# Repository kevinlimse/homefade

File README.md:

# homefade

Wall-mounted motorized fader for Home Assistant (brightness / colour temp, live two-way sync), 18 mm pitch so 2–3 sit side by side.

- `HANDOVER.md` – status, chosen parts, open items, how to set up a new machine.
- `pcb/` – KiCad project, Gerbers/BOM/CPL (`pcb/fab/`), ESPHome firmware (`pcb/esphome/`), generator scripts (`pcb/gen/`).
- `cad/` – FreeCAD fader model and PCBA assembly (FCStd + STEP).
- `freecad-macros/` – macros to copy into `%APPDATA%\FreeCAD\v1-1\Macro\`.

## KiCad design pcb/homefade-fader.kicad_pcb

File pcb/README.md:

# homefade fader controller v1.1

One small board per Alps RS60N11M9A0F motor fader. It connects the fader to Home Assistant through ESPHome, with live sync both ways.

## Why one board per fader (and not one board for three)

* **Width = fader width.** The board is **18.0 mm wide**, the same as the fader frame, and hangs directly on the fader's own pins. Faders can sit side by side at an **18 mm pitch** (frames touching). A 3-fader board would fix the spacing forever and still be ≥ 54 mm wide.
* **Flat back.** Every SMD part sits on the side facing the fader, in the space under its body (the fader seats 26 mm below the panel, and most of that is empty). The back of the PCB is flat apart from the soldered fader pins, so total depth is about **26 mm + 1.6 mm PCB + ~1.5 mm of pin tails**.
* **One USB-C feeds several.** Plug USB-C into one board. Wire its **J2 (VBUS/GND)** pads to J2 on the next board(s). Only plug one USB-C into a chained set. A 9 V / 2 A (18 W+) charger is plenty for 3 faders.
* Each fader becomes its own ESPHome device. They're independent, and one bad board doesn't take the others down. An ESP32-S3 costs about $3.

Board: **18.0 × 120.0 mm**, **4 layers** (inner 1 = solid GND plane), 1.6 mm. Coordinates match the FreeCAD model (X = 0 at the fader's 3T end). The board runs 6 mm past the 3T end for the USB-C and 7.5 mm past the 1T end, so the Wi-Fi antenna isn't under the motor.

## Blocks

| Block | Part | Notes |
|---|---|---|
| Power in | USB-C (HRO TYPE-C-31-M-12) + **CH224A** PD sink | Asks for **9 V** (R3 = 6.8 k). For 12 V, fit 24 k (C25769) and set `max_duty: 0.83`. Never leave R3 open: open = 20 V, which kills the TB6612. Most chargers do 9 V; many (Apple, for example) don't offer 12 V. |
| ESD | USBLC6-2SC6 | On D+/D− |
| 3.3 V | TPS563201 buck, 3.3 µH, 33 k/10 k | 4.5–17 V in |
| Motor | **TB6612FNG**, both bridges in parallel | 15 V max; brake/coast; STBY pulled low while the ESP boots |
| MCU | **ESP32-S3-MINI-1-N8** | Native USB on the same USB-C for flashing and logs (no USB-UART chip). Built-in capacitive touch is used for the fader's touch track. |
| Fader | pot (via 1 k from 3V3 so the wiper tops out at ~3.0 V), RC filter → GPIO1; touch "T" → GPIO2 | Frame lugs to GND |
| Extra | BOOT/RESET buttons, LED (GPIO10), VBUS sense (GPIO9, ÷11), PD power-good (GPIO8) | The firmware won't drive the motor without PD power (for example when it's only on a PC port at 5 V) |
| Position LED bar | 10 × **SK6812SIDE-A** side-firing RGB LEDs (GPIO17, 100 Ω), 2nd TPS563201 at **4.5 V** (33k/6.8k, 4×4 mm 3.3 µH) | One LED per 10 % of travel along the +Y edge, light exits sideways from under the fader. At 4.5 V the LED input threshold (0.65 × VDD = 2.9 V) is below the ESP's 3.3 V, so no level shifter. Worst case all-white ≈ 360 mA from 4.5 V |

GPIO map: 1 wiper ADC, 2 touch, 4 PWM, 5 IN1, 6 IN2, 7 STBY, 8 PD_PG, 9 VBUS sense, 10 LED, 17 LED bar data, 19/20 USB.

## Files

* `homefade-fader.kicad_pro / .kicad_sch / .kicad_pcb`: KiCad 7+ project. Schematic uses net labels.
* `board-routed.png`: top and bottom copper.
* `fab/homefade-fader-gerbers-JLCPCB.zip`: Gerbers and Excellon drill files, ready to upload (**4 layers**, 1.6 mm, JLC default stackup).
* `homefade.pretty`, `homefade.kicad_sym`: project footprints and symbols (fader footprint from the Alps drawing, Espressif's official ESP32-S3-MINI-1 footprint).
* `fab/BOM-JLCPCB.csv`, `fab/CPL-JLCPCB.csv`, `fab/BOM.md`: JLCPCB assembly files. Every part was in stock at LCSC on 2026-11-26.
* `esphome/homefade-fader.yaml`: firmware (validated with `esphome config`, ESPHome 2026.11).
* `gen/`: Python scripts that generate everything from `gen/design.py`. `route_all.sh` re-runs placement → Freerouting → finishing router → stitching.

## Status / before ordering

1. **v1.1 adds the position LED bar and goes to 4 layers.** With the LED row along one edge, a 2-layer board could not keep its ground pours joined (the motor driver's ground ended up on an island), so inner layer 1 is now a solid GND plane and inner layer 2 carries signals. Freerouting did the signals; `gen/ledbar_route.py` pre-routes the LED row (4.5 V rail under the LEDs, data hops just inboard, a GND via per LED). KiCad DRC: **0 unconnected pads, no clearance, width or hole errors**; only cosmetic silk and library-path warnings remain.
2. **LED footprint is [EST].** The SK6812SIDE-A land pattern is only drawn (not dimensioned in text) in the datasheet. I used 4 pads, 0.7 × 1.1 mm at 1.15 mm pitch at the rear of the 4.0 × 1.6 mm body, light out of the long front face, pin 1 = DIN. **Check it, and that each LED faces the board edge, in JLC's footprint/CPL preview before ordering.** Same for **U1 (CH224A ESSOP-10)** and **L1 (FXL0630)**.
3. The fader's under-body heights are **[EST]** in the FreeCAD model. Parts under the motor (x 66–92 mm) are ≤ 2.1 mm tall; the model gives ~5 mm of space. The LEDs sit at y 7.4–9.0 mm, just outside the motor bracket (±7 mm [EST]) at x 61–65 mm. Check against a real fader.
4. Antenna: keep metal off the board end past the fader (x > 106.5 mm). A metal faceplate 26 mm above will reduce range somewhat.
5. In HA, allow the device to perform Home Assistant actions (ESPHome integration → Configure).

## Firmware tuning (first boot)

1. Watch **Fader raw** in the logs at both ends of travel. Put the values in `adc_bottom` / `adc_top`.
2. Set `esp32_touch: setup_mode: true`, then touch and release the knob. Choose `touch_threshold` between the two values (S3 values *rise* when touched).
3. If the fader runs away from the target, set `motor_invert: "true"`. Raise `min_duty` if it stalls near the target; lower `kp` if it overshoots.
4. LED bar: if it fills from the wrong end, set `led_bar_reverse: "true"`. In HA, **Position bar** switches the LEDs and sets overall brightness; **Bar filled colour** (default green) and **Bar empty colour** (default dim red) are colour pickers for the part below and above the knob.

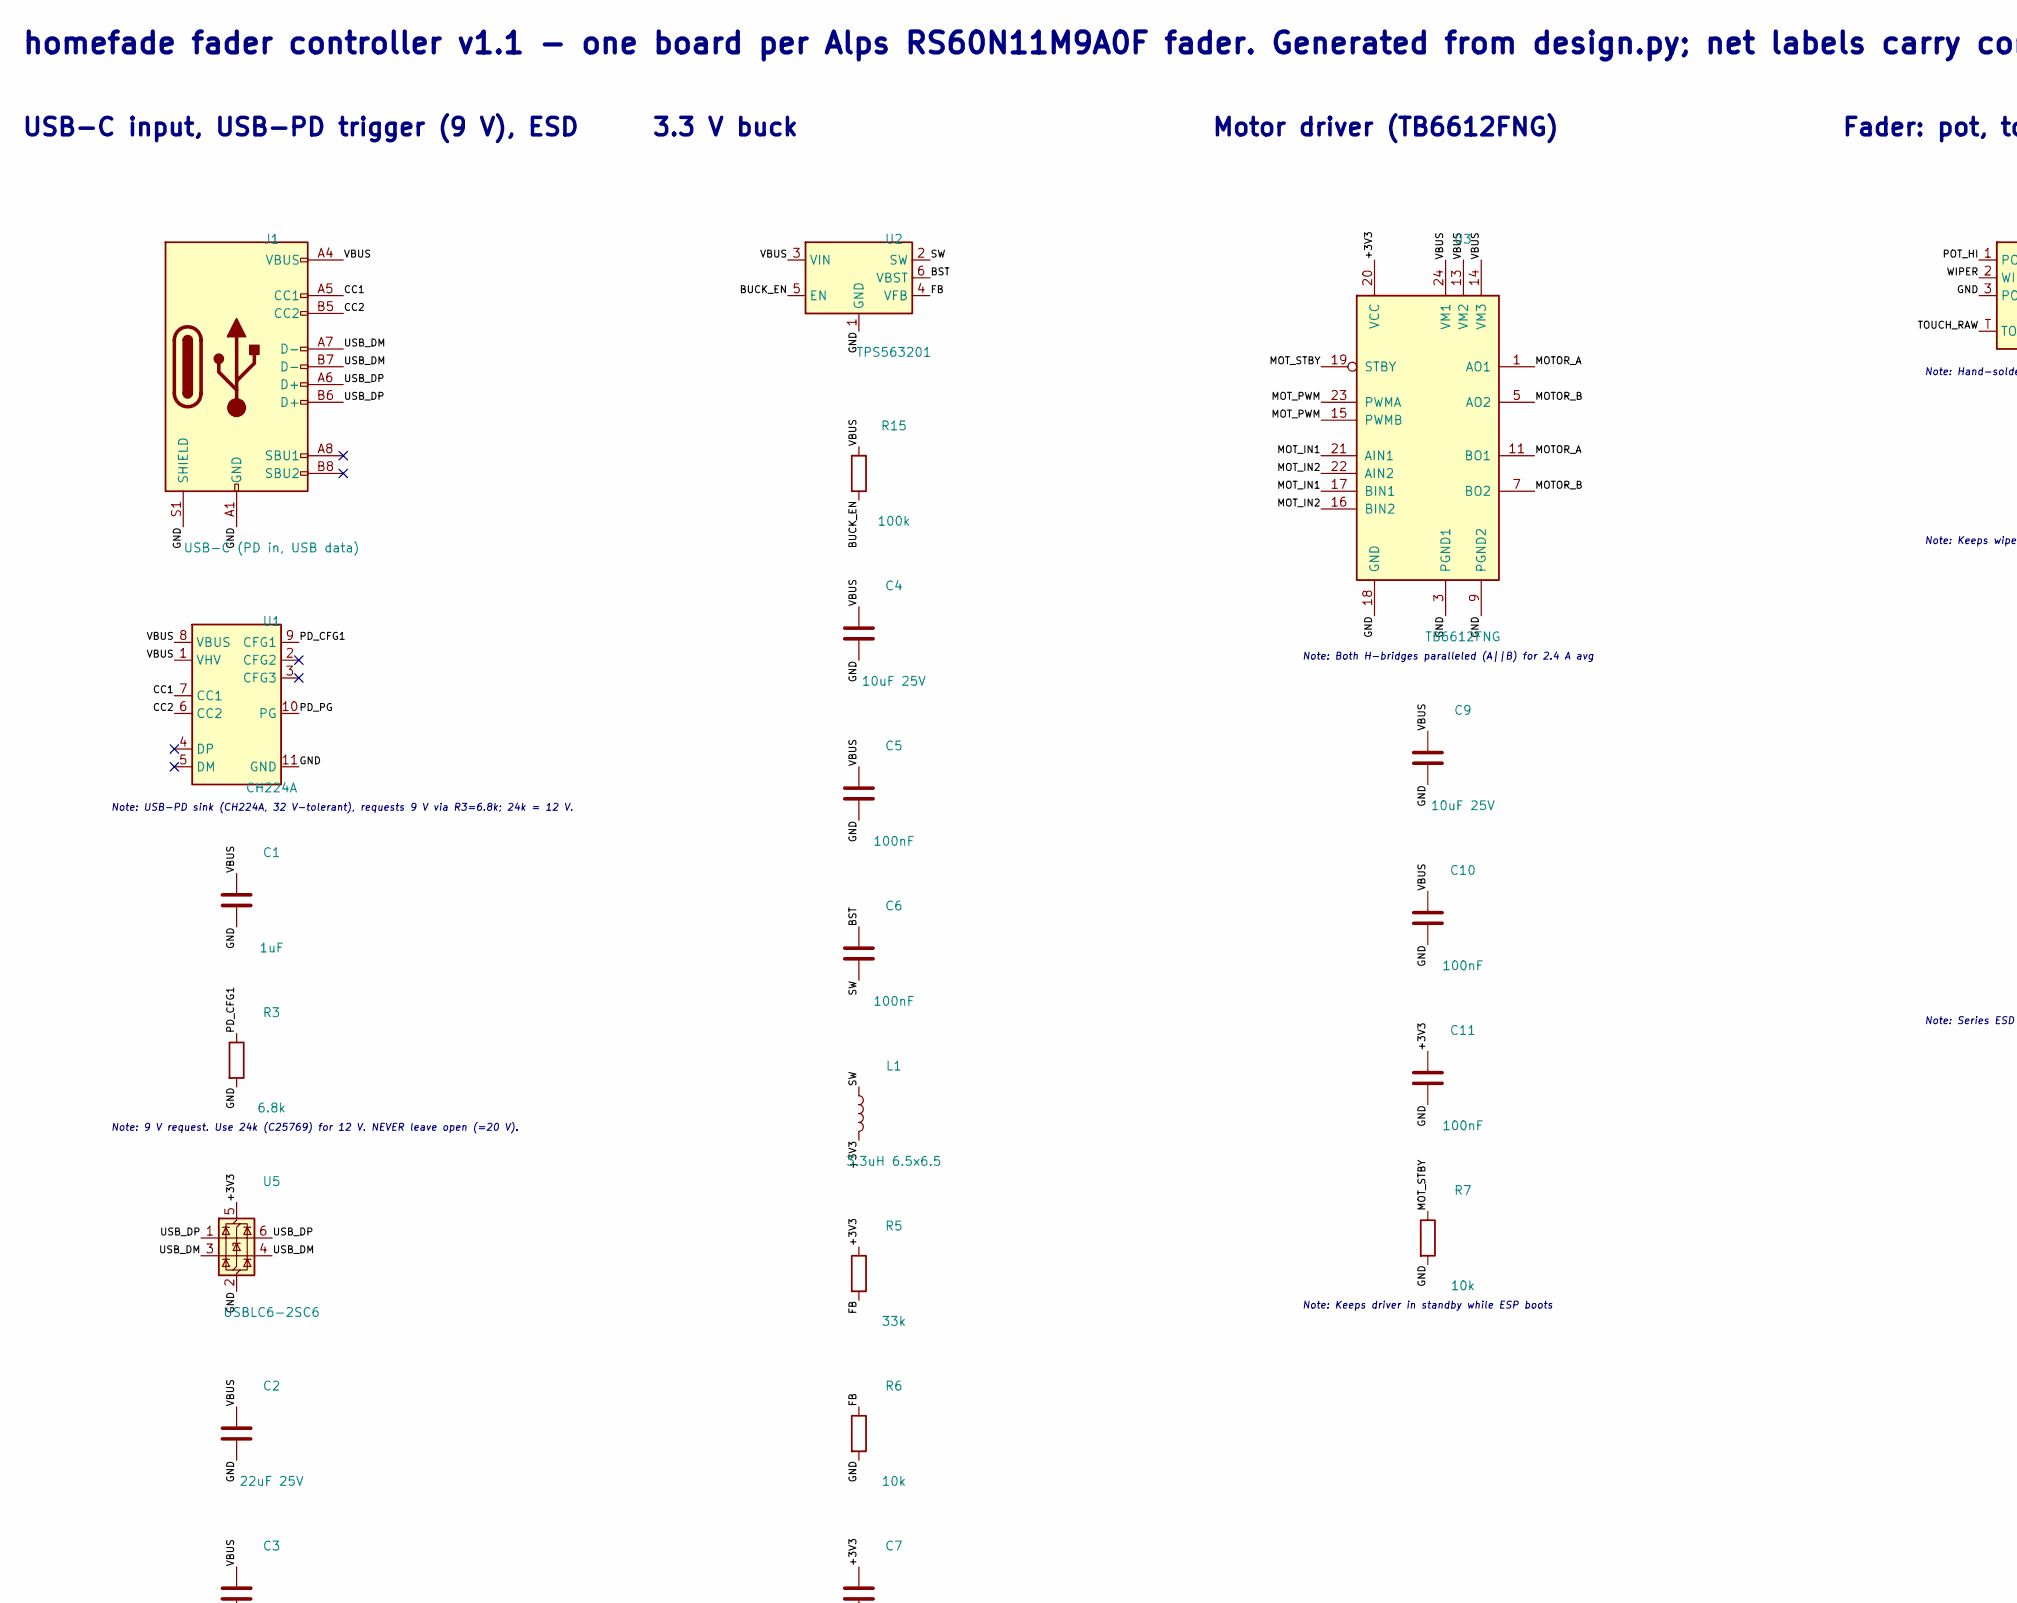
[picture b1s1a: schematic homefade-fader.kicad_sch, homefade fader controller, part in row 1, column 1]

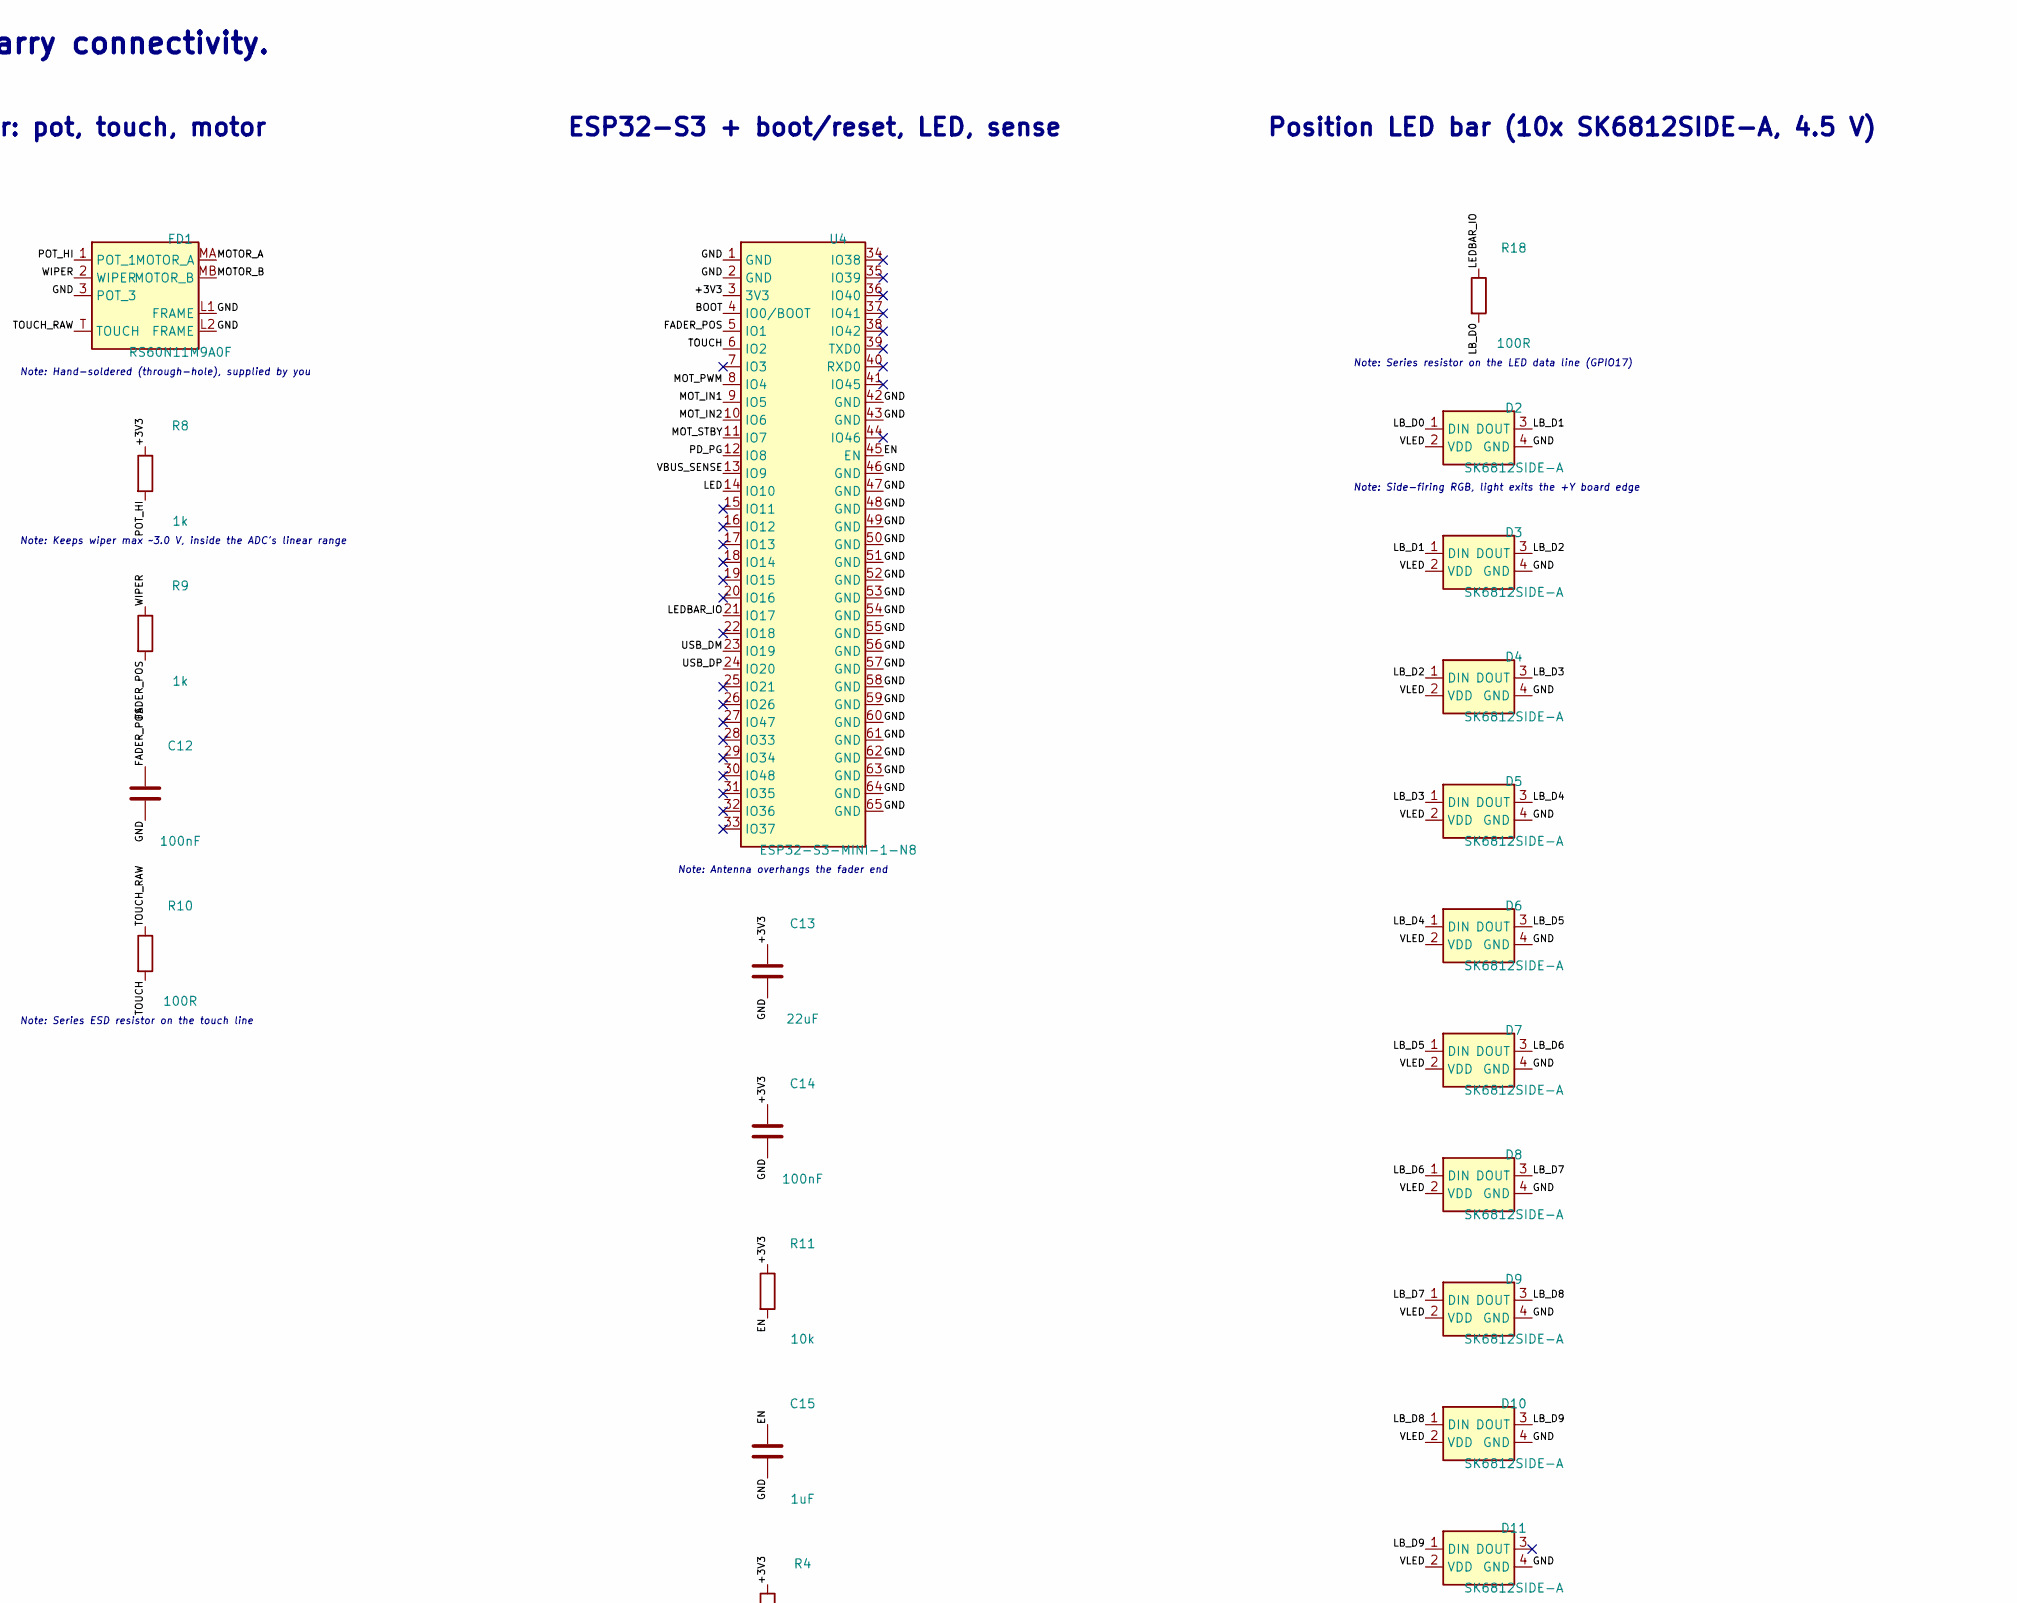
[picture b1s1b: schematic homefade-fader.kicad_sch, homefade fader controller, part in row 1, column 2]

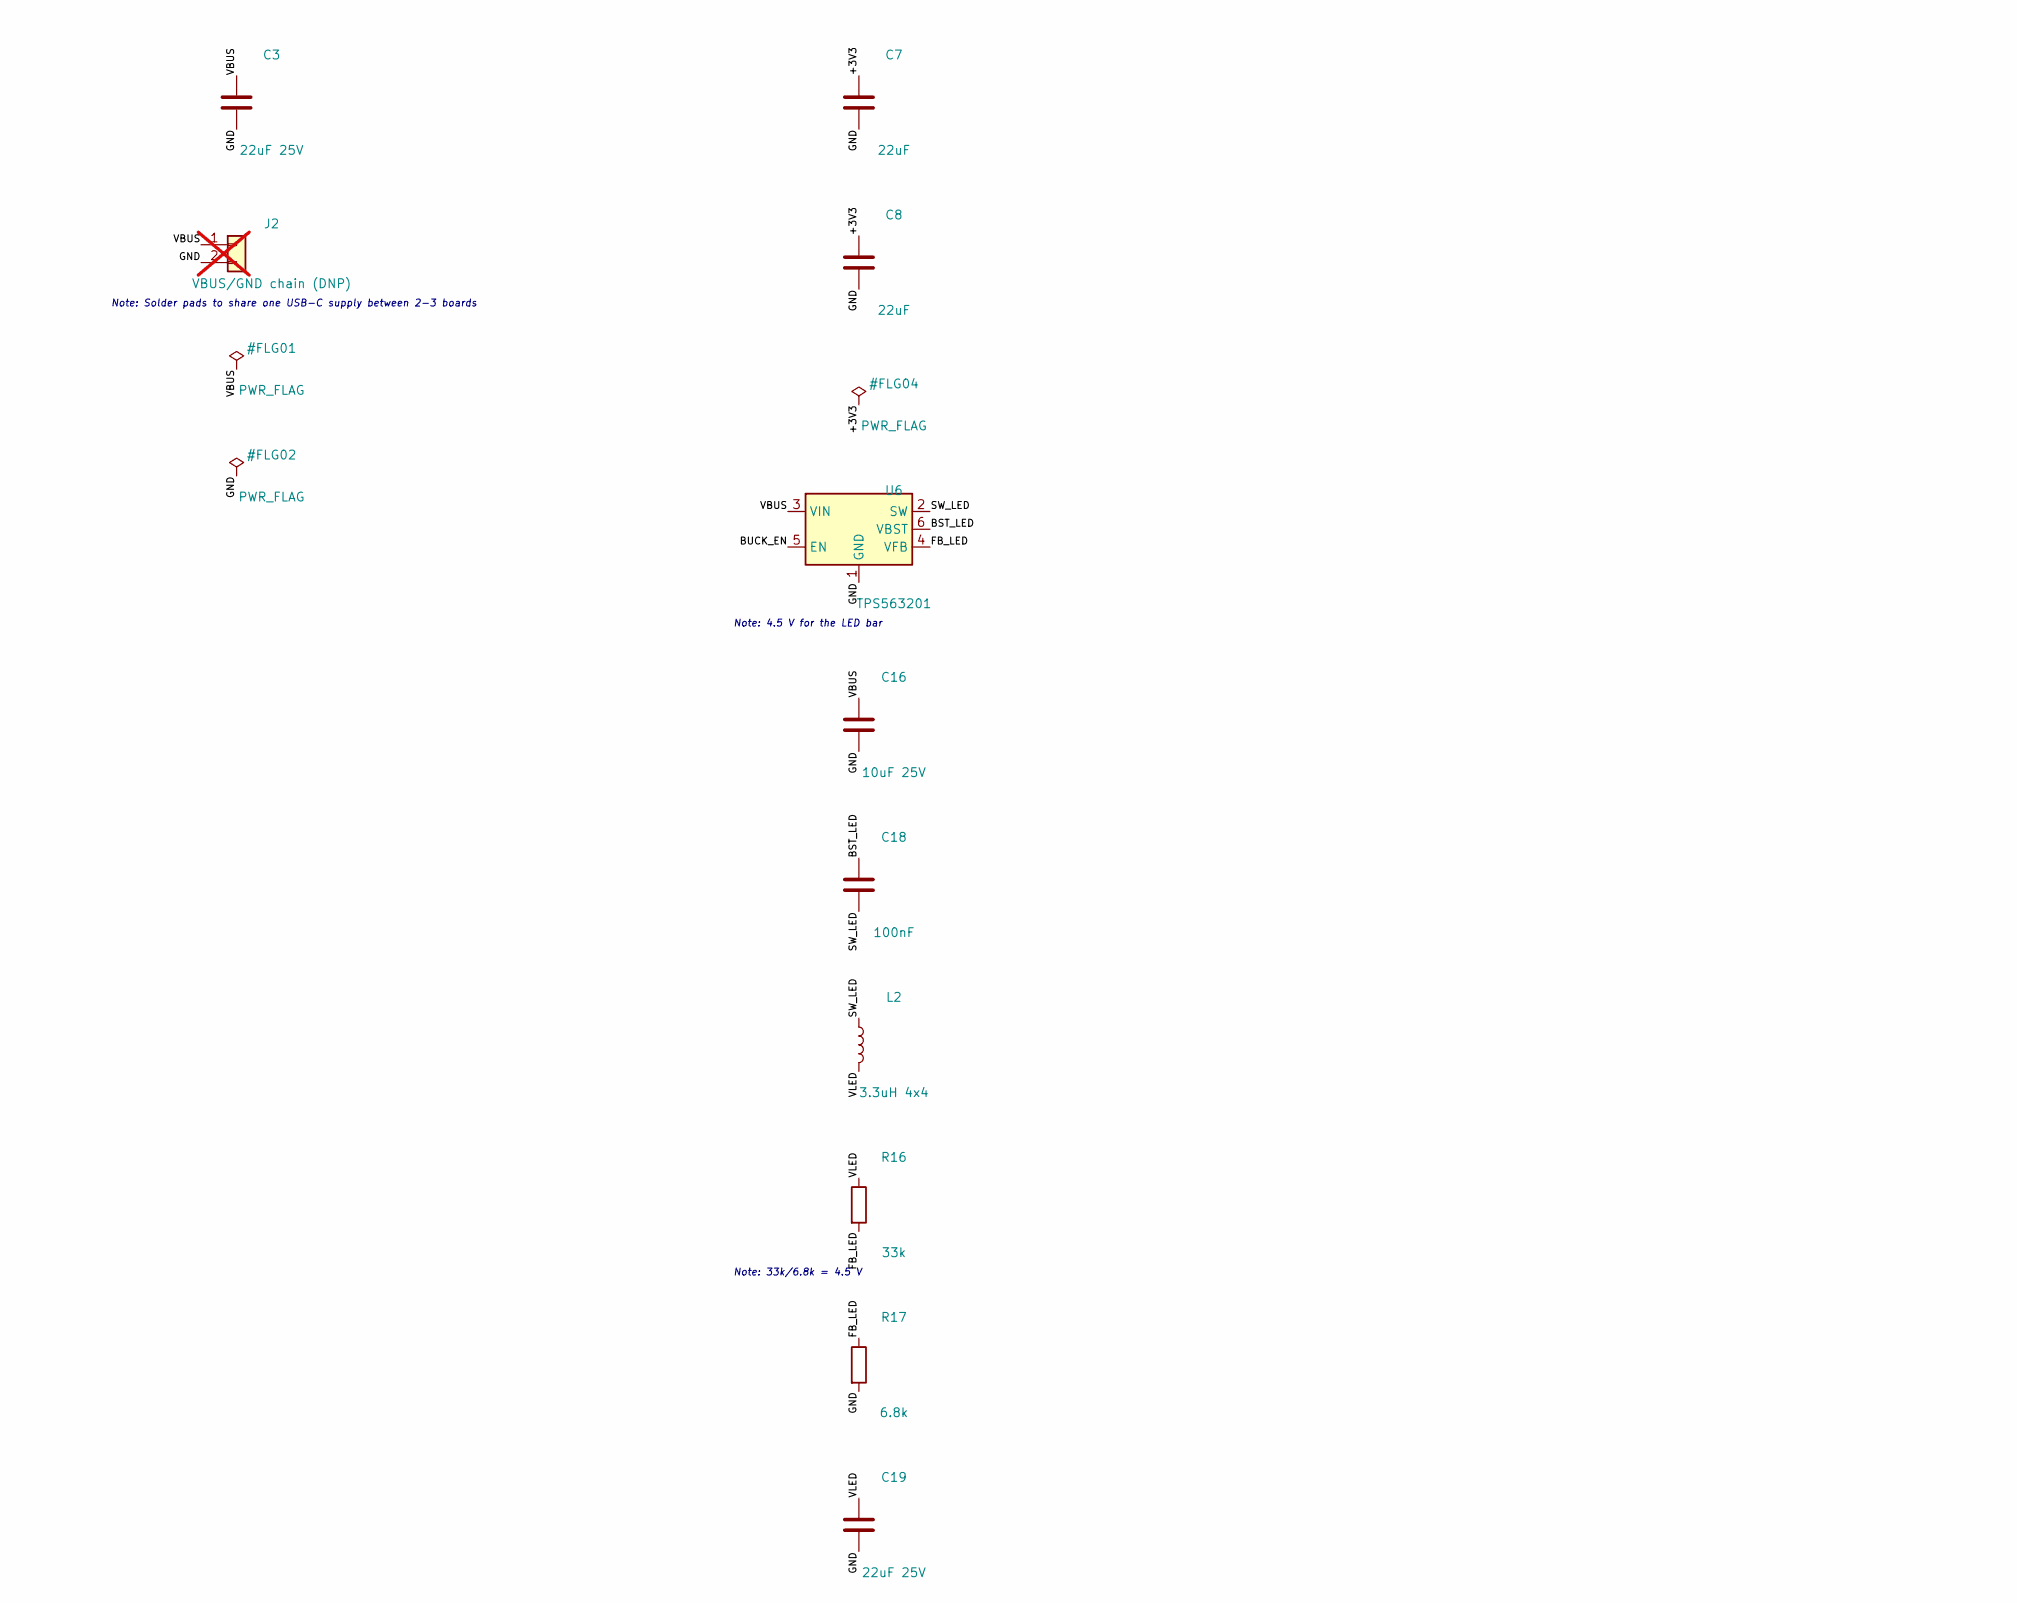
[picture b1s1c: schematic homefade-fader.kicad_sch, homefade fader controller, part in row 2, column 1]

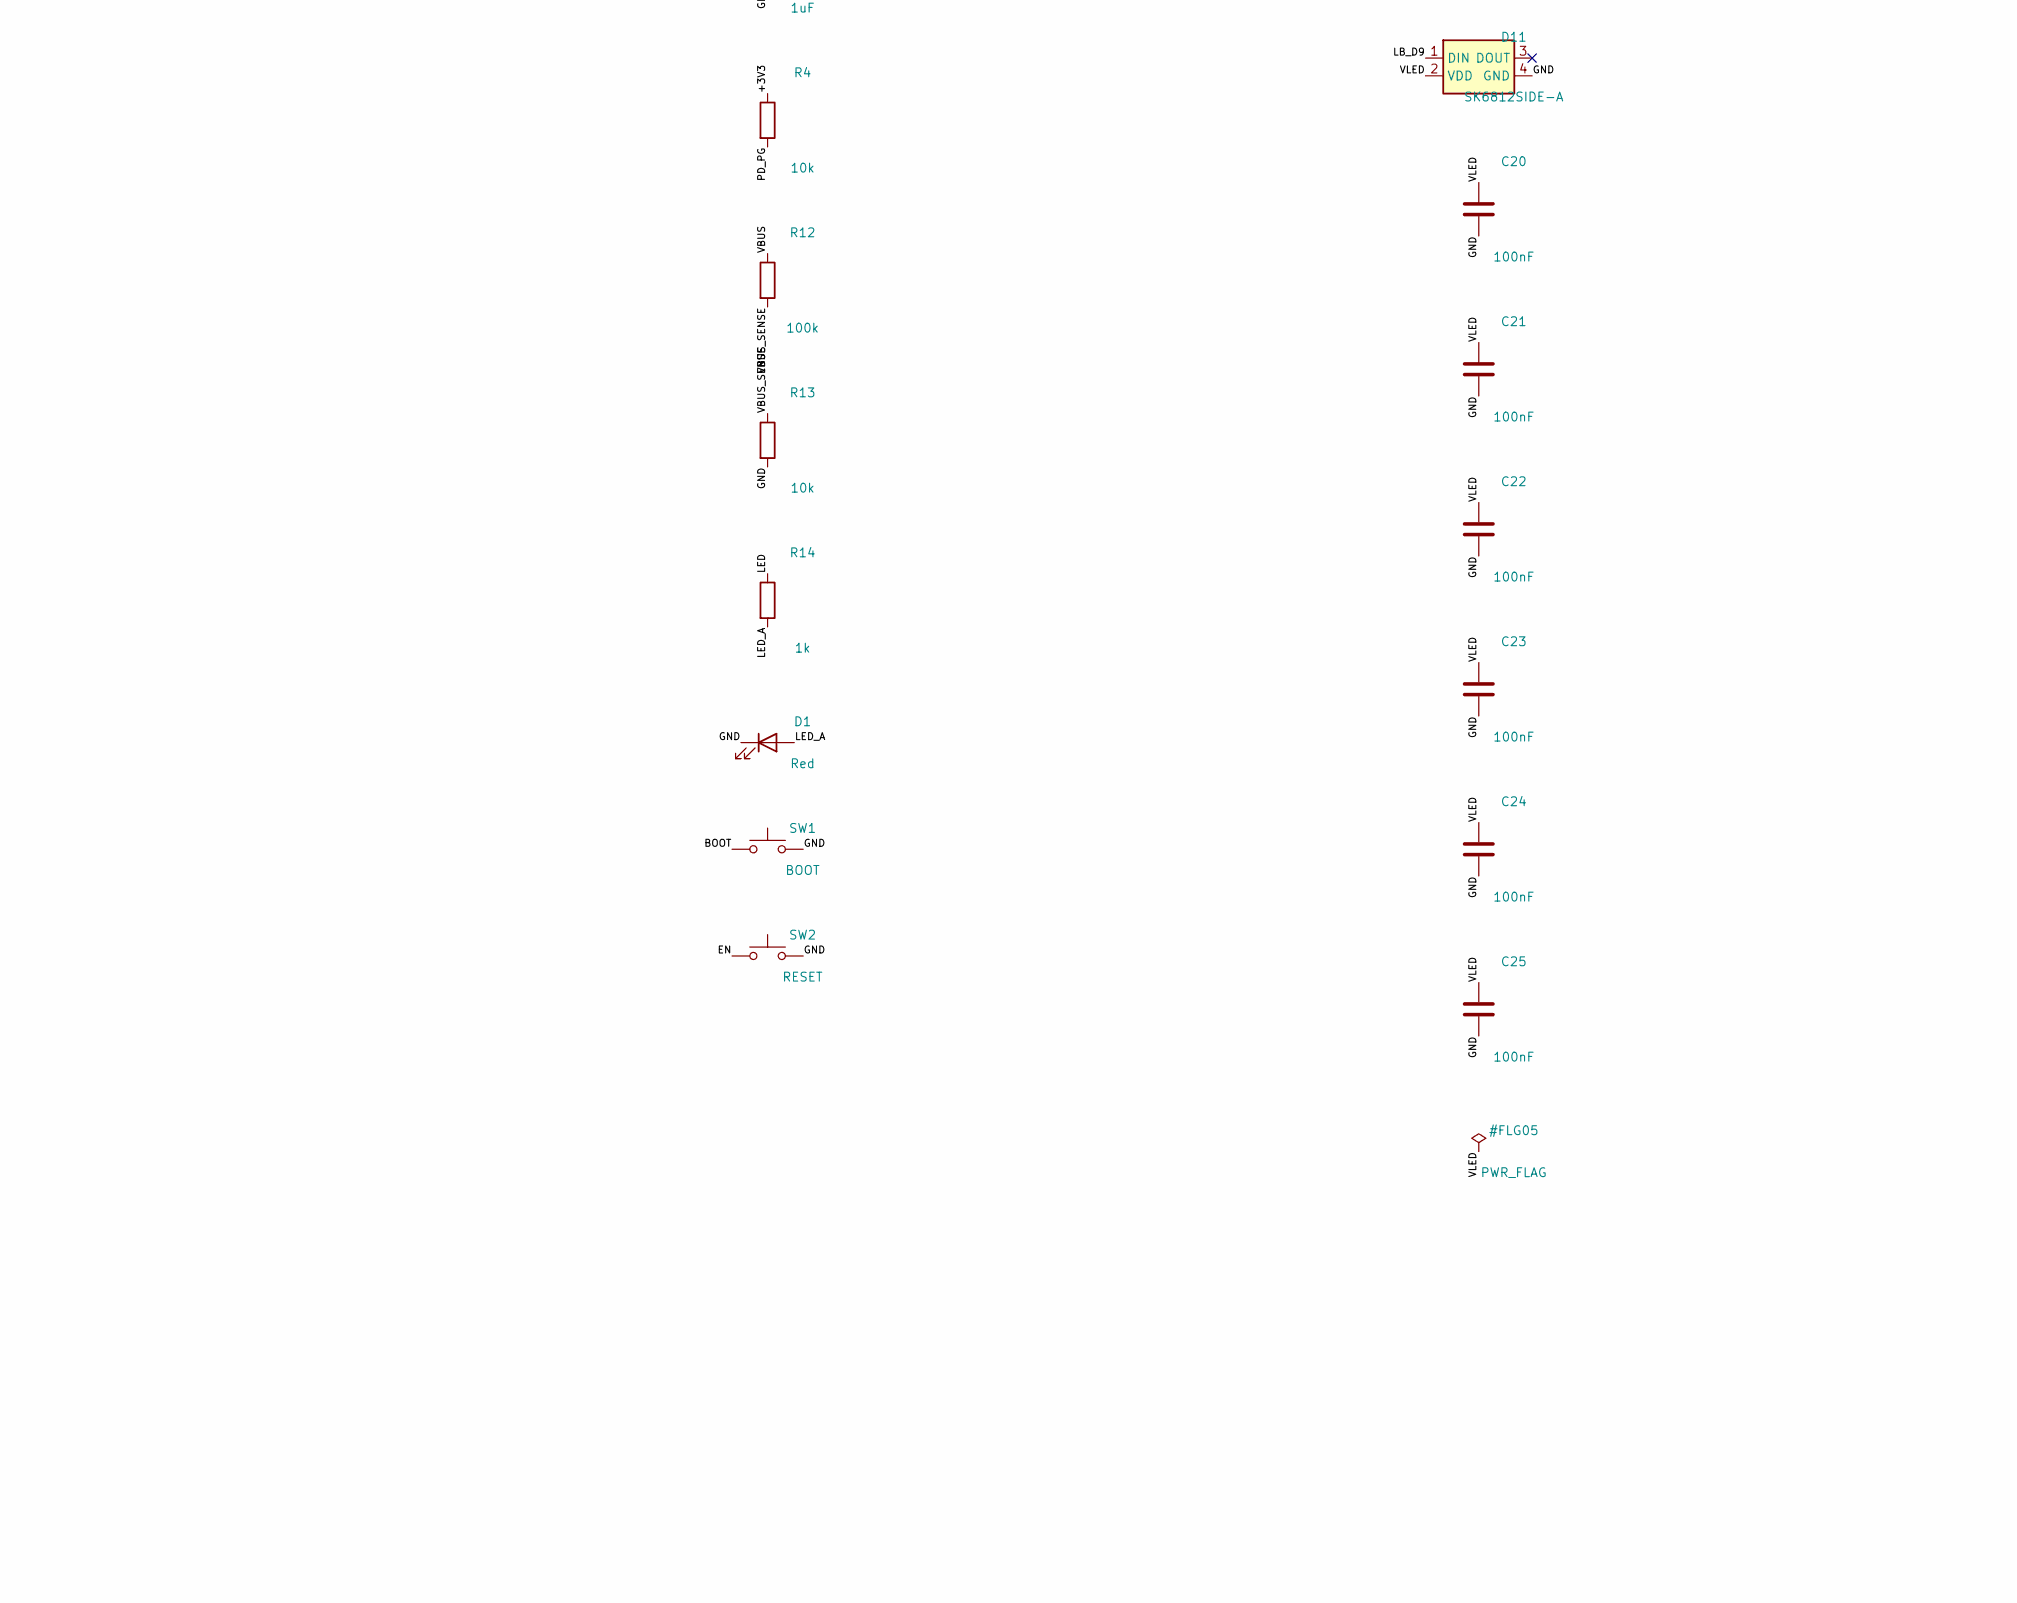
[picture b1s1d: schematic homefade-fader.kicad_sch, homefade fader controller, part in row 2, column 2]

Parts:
C1, C15: 1uF; C_0402_1005Metric; LCSC C83063
C2, C3, C19: 22uF 25V; C_0805_2012Metric; LCSC C45783
C4, C9, C16: 10uF 25V; C_0603_1608Metric; LCSC C96446
C5, C6, C10, C11, C12, C14, C18, C20, C21, C22, C23, C24, C25: 100nF; C_0402_1005Metric; LCSC C1525
C7, C8, C13: 22uF; C_0603_1608Metric; LCSC C59461
D1: Red; LED_0603_1608Metric; LCSC C2286
D2, D3, D4, D5, D6, D7, D8, D9, D10, D11: SK6812SIDE-A; LED_SK6812SIDE-A_4.0x1.6mm; LCSC C5378721
FD1: RS60N11M9A0F; Alps_RS60N11M9_Fader
J1: USB-C (PD in, USB data); USB_C_Receptacle_HRO_TYPE-C-31-M-12; LCSC C165948
J2: VBUS/GND chain (DNP); PinHeader_1x02_P2.54mm_Vertical; not fitted
L1: 3.3uH 6.5x6.5; L_FXL0630; LCSC C167219
L2: 3.3uH 4x4; L_Changjiang_FNR4020S; LCSC C167826
R3, R17: 6.8k; R_0402_1005Metric; LCSC C25917
R4, R6, R7, R11, R13: 10k; R_0402_1005Metric; LCSC C25744
R5, R16: 33k; R_0402_1005Metric; LCSC C25779
R8, R9, R14: 1k; R_0402_1005Metric; LCSC C11702
R10, R18: 100R; R_0402_1005Metric; LCSC C25076
R12, R15: 100k; R_0402_1005Metric; LCSC C25741
SW1: BOOT; SW_Push_1P1T_XKB_TS-1187A; LCSC C318884
SW2: RESET; SW_Push_1P1T_XKB_TS-1187A; LCSC C318884
U1: CH224A; ESSOP-10_3.9x4.9mm_P1.0mm_EP; LCSC C42459160
U2, U6: TPS563201; SOT-23-6; LCSC C116592
U3: TB6612FNG; SSOP-24_5.3x8.2mm_P0.65mm; LCSC C88224
U4: ESP32-S3-MINI-1-N8; ESP32-S3-MINI-1; LCSC C2913206
U5: USBLC6-2SC6; SOT-23-6; LCSC C7519

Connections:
+3V3: C7.1, C8.1, C11.1, C13.1, C14.1, L1.2, R4.1, R5.1, R8.1, R11.1, U3.20 (VCC), U4.3 (3V3), U5.5 (VBUS)
BOOT: SW1.1, U4.4 (IO0/BOOT)
BST: C6.1, U2.6 (VBST)
BST_LED: C18.1, U6.6 (VBST)
BUCK_EN: R15.2, U2.5 (EN), U6.5 (EN)
CC1: J1.A5 (CC1), U1.7 (CC1)
CC2: J1.B5 (CC2), U1.6 (CC2)
EN: C15.1, R11.2, SW2.1, U4.45 (EN)
FADER_POS: C12.1, R9.2, U4.5 (IO1)
FB: R5.2, R6.1, U2.4 (VFB)
FB_LED: R16.2, R17.1, U6.4 (VFB)
GND: C1.2, C2.2, C3.2, C4.2, C5.2, C7.2, C8.2, C9.2, C10.2, C11.2, C12.2, C13.2, C14.2, C15.2, C16.2, C19.2, C20.2, C21.2, C22.2, C23.2, C24.2, C25.2, D1.1 (K), D2.4 (GND), D3.4 (GND), D4.4 (GND), D5.4 (GND), D6.4 (GND), D7.4 (GND), D8.4 (GND), D9.4 (GND), D10.4 (GND), D11.4 (GND), FD1.3 (POT_3), FD1.L1 (FRAME), FD1.L2 (FRAME), J1.A1 (GND), J1.A12 (GND), J1.B1 (GND), J1.B12 (GND), J1.S1 (SHIELD), J2.2, R3.2, R6.2, R7.2, R13.2, R17.2, SW1.2, SW2.2, U1.11 (GND), U2.1 (GND), U3.3 (PGND1), U3.4 (PGND1), U3.9 (PGND2), U3.10 (PGND2), U3.18 (GND), U4.1 (GND), U4.2 (GND), U4.42 (GND), U4.43 (GND), U4.46 (GND), U4.47 (GND), U4.48 (GND), U4.49 (GND), U4.50 (GND), U4.51 (GND), U4.52 (GND), U4.53 (GND), U4.54 (GND), U4.55 (GND), U4.56 (GND), U4.57 (GND), U4.58 (GND), U4.59 (GND), U4.60 (GND), U4.61 (GND), U4.62 (GND), U4.63 (GND), U4.64 (GND), U4.65 (GND), U5.2 (GND), U6.1 (GND)
LB_D0: D2.1 (DIN), R18.2
LB_D1: D2.3 (DOUT), D3.1 (DIN)
LB_D2: D3.3 (DOUT), D4.1 (DIN)
LB_D3: D4.3 (DOUT), D5.1 (DIN)
LB_D4: D5.3 (DOUT), D6.1 (DIN)
LB_D5: D6.3 (DOUT), D7.1 (DIN)
LB_D6: D7.3 (DOUT), D8.1 (DIN)
LB_D7: D8.3 (DOUT), D9.1 (DIN)
LB_D8: D9.3 (DOUT), D10.1 (DIN)
LB_D9: D10.3 (DOUT), D11.1 (DIN)
LED: R14.1, U4.14 (IO10)
LEDBAR_IO: R18.1, U4.21 (IO17)
LED_A: D1.2 (A), R14.2
MOTOR_A: FD1.MA (MOTOR_A), U3.1 (AO1), U3.2 (AO1), U3.11 (BO1), U3.12 (BO1)
MOTOR_B: FD1.MB (MOTOR_B), U3.5 (AO2), U3.6 (AO2), U3.7 (BO2), U3.8 (BO2)
MOT_IN1: U3.17 (BIN1), U3.21 (AIN1), U4.9 (IO5)
MOT_IN2: U3.16 (BIN2), U3.22 (AIN2), U4.10 (IO6)
MOT_PWM: U3.15 (PWMB), U3.23 (PWMA), U4.8 (IO4)
MOT_STBY: R7.1, U3.19 (STBY), U4.11 (IO7)
PD_CFG1: R3.1, U1.9 (CFG1)
PD_PG: R4.2, U1.10 (PG), U4.12 (IO8)
POT_HI: FD1.1 (POT_1), R8.2
SW: C6.2, L1.1, U2.2 (SW)
SW_LED: C18.2, L2.1, U6.2 (SW)
TOUCH: R10.2, U4.6 (IO2)
TOUCH_RAW: FD1.T (TOUCH), R10.1
USB_DM: J1.A7 (D-), J1.B7 (D-), U4.23 (IO19), U5.3 (I/O2), U5.4 (I/O2)
USB_DP: J1.A6 (D+), J1.B6 (D+), U4.24 (IO20), U5.1 (I/O1), U5.6 (I/O1)
VBUS: C1.1, C2.1, C3.1, C4.1, C5.1, C9.1, C10.1, C16.1, J1.A4 (VBUS), J1.A9 (VBUS), J1.B4 (VBUS), J1.B9 (VBUS), J2.1, R12.1, R15.1, U1.1 (VHV), U1.8 (VBUS), U2.3 (VIN), U3.13 (VM2), U3.14 (VM3), U3.24 (VM1), U6.3 (VIN)
VBUS_SENSE: R12.2, R13.1, U4.13 (IO9)
VLED: C19.1, C20.1, C21.1, C22.1, C23.1, C24.1, C25.1, D2.2 (VDD), D3.2 (VDD), D4.2 (VDD), D5.2 (VDD), D6.2 (VDD), D7.2 (VDD), D8.2 (VDD), D9.2 (VDD), D10.2 (VDD), D11.2 (VDD), L2.2, R16.1
WIPER: FD1.2 (WIPER), R9.1

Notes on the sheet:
USB-C input, USB-PD trigger (9 V), ESD
3.3 V buck
Motor driver (TB6612FNG)
Fader: pot, touch, motor
ESP32-S3 + boot/reset, LED, sense
Position LED bar (10x SK6812SIDE-A, 4.5 V)
Note: USB-PD sink (CH224A, 32 V-tolerant), requests 9 V via R3=6.8k; 24k = 12 V.
Note: 9 V request. Use 24k (C25769) for 12 V. NEVER leave open (=20 V).
Note: Solder pads to share one USB-C supply between 2-3 boards
Note: Both H-bridges paralleled (A||B) for 2.4 A avg
Note: Keeps driver in standby while ESP boots
Note: Hand-soldered (through-hole), supplied by you
Note: Keeps wiper max ~3.0 V, inside the ADC's linear range
Note: Series ESD resistor on the touch line
Note: Antenna overhangs the fader end
Note: 4.5 V for the LED bar
Note: 33k/6.8k = 4.5 V
Note: Series resistor on the LED data line (GPIO17)
Note: Side-firing RGB, light exits the +Y board edge
homefade fader controller v1.1 - one board per Alps RS60N11M9A0F fader. Generated from design.py; net labels carry connectivity.

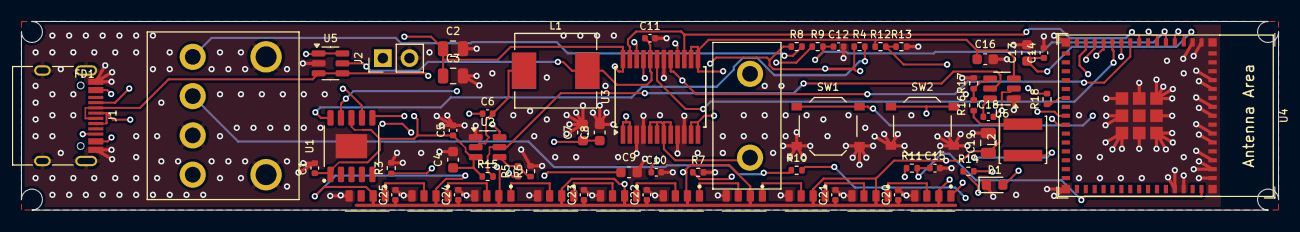
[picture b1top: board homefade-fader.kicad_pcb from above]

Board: 4 copper layers, 120.0 x 18.0 mm, 64 parts (0 on the bottom side), 44 nets.

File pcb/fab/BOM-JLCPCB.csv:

Comment,Designator,Footprint,LCSC Part #
"USB-C (PD in, USB data)",J1,USB_C_Receptacle_HRO_TYPE-C-31-M-12,C165948
CH224A,U1,ESSOP-10_3.9x4.9mm_P1.0mm_EP,C42459160
1uF,"C1,C15",C_0402_1005Metric,C83063
6.8k,"R3,R17",R_0402_1005Metric,C25917
USBLC6-2SC6,U5,SOT-23-6,C7519
22uF 25V,"C2,C3,C19",C_0805_2012Metric,C45783
TPS563201,"U2,U6",SOT-23-6,C116592
100k,"R15,R12",R_0402_1005Metric,C25741
10uF 25V,"C4,C9,C16",C_0603_1608Metric,C96446
100nF,"C5,C6,C10,C11,C12,C14,C18,C20,C21,C22,C23,C24,C25",C_0402_1005Metric,C1525
3.3uH 6.5x6.5,L1,L_FXL0630,C167219
33k,"R5,R16",R_0402_1005Metric,C25779
10k,"R6,R7,R11,R4,R13",R_0402_1005Metric,C25744
22uF,"C7,C8,C13",C_0603_1608Metric,C59461
TB6612FNG,U3,SSOP-24_5.3x8.2mm_P0.65mm,C88224
1k,"R8,R9,R14",R_0402_1005Metric,C11702
100R,"R10,R18",R_0402_1005Metric,C25076
ESP32-S3-MINI-1-N8,U4,ESP32-S3-MINI-1,C2913206
Red,D1,LED_0603_1608Metric,C2286
BOOT,SW1,SW_Push_1P1T_XKB_TS-1187A,C318884
RESET,SW2,SW_Push_1P1T_XKB_TS-1187A,C318884
3.3uH 4x4,L2,L_Changjiang_FNR4020S,C167826
SK6812SIDE-A,"D2,D3,D4,D5,D6,D7,D8,D9,D10,D11",LED_SK6812SIDE-A_4.0x1.6mm,C5378721
